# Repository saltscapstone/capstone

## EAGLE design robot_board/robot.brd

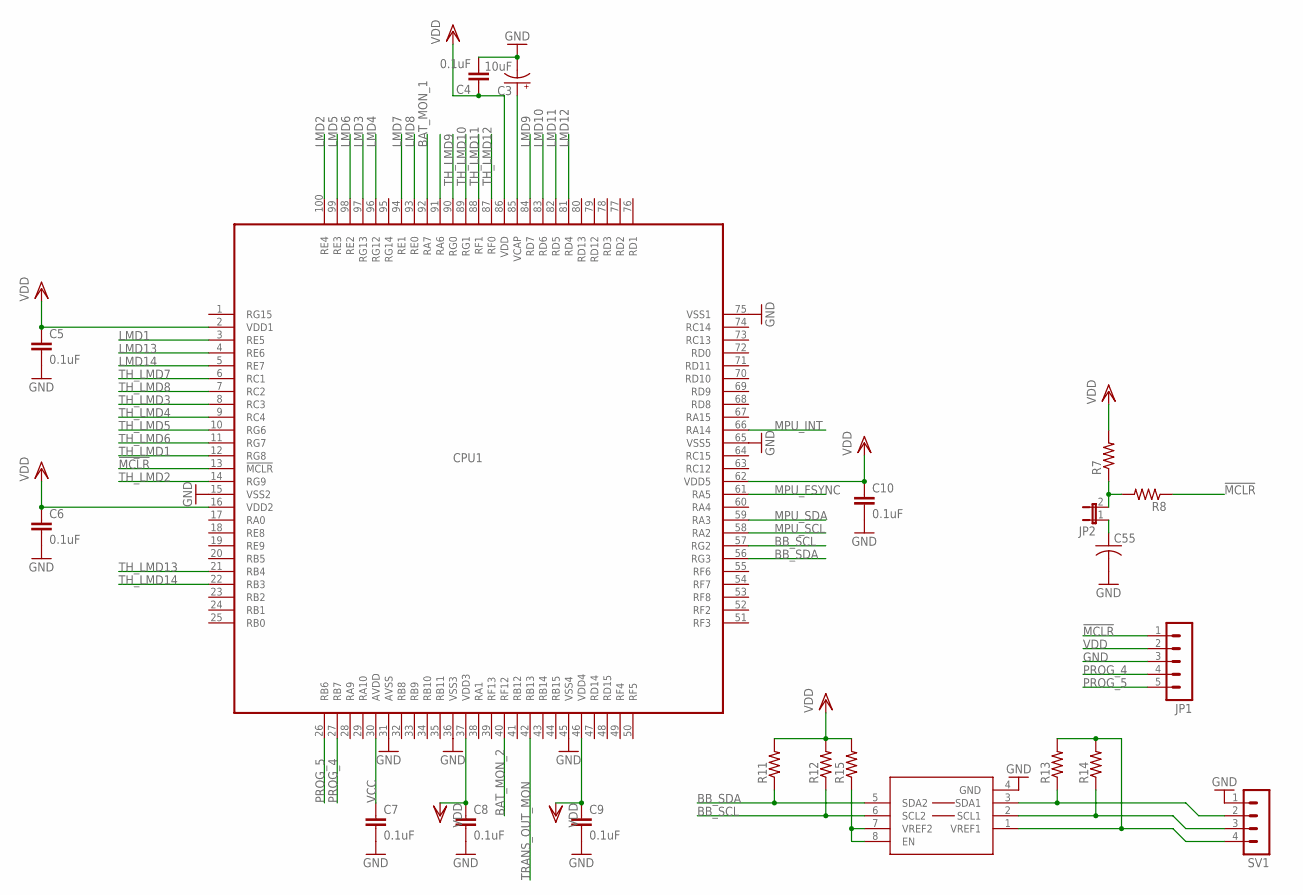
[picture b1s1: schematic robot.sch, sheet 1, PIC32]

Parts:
C3: 10uF; EIA3216
C4, C5, C6, C7, C8, C9, C10: 0.1uF; 0402-CAP
C55: C-USC0603; C0603
CPU1: DSPIC33FJ32GS610TQFP; TQFP100-14X14
JP1: MA05-1
JP2: JP1E; JP1
R7, R8, R11, R12, R13, R14, R15: R-US_R0603; R0603
SV1: MA04-1
U$17: PCA9306; PSOP-8

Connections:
!MCLR: CPU1.13 (!MCLR), JP1.1, R8.1
BAT_MON_1: CPU1.92 (RA7); also elsewhere on the board
BAT_MON_2: CPU1.40 (RF12); also elsewhere on the board
BB_SCL: CPU1.57 (RG2), R12.1, U$17.6 (SCL2)
BB_SDA: CPU1.56 (RG3), R11.1, U$17.5 (SDA2)
GND: C3.C (-), C4.2, C5.2, C6.2, C7.2, C8.2, C9.2, C10.2, C55.2, CPU1.15 (VSS2), CPU1.31 (AVSS), CPU1.36 (VSS3), CPU1.45 (VSS4), CPU1.65 (VSS5), CPU1.75 (VSS1), JP1.3, SV1.1, U$17.4 (GND); also elsewhere on the board
LMD1: CPU1.3 (RE5); also elsewhere on the board
LMD2: CPU1.100 (RE4); also elsewhere on the board
LMD3: CPU1.97 (RG13); also elsewhere on the board
LMD4: CPU1.96 (RG12); also elsewhere on the board
LMD5: CPU1.99 (RE3); also elsewhere on the board
LMD6: CPU1.98 (RE2); also elsewhere on the board
LMD7: CPU1.94 (RE1); also elsewhere on the board
LMD8: CPU1.93 (RE0); also elsewhere on the board
LMD9: CPU1.84 (RD7); also elsewhere on the board
LMD10: CPU1.83 (RD6); also elsewhere on the board
LMD11: CPU1.82 (RD5); also elsewhere on the board
LMD12: CPU1.81 (RD4); also elsewhere on the board
LMD13: CPU1.4 (RE6); also elsewhere on the board
LMD14: CPU1.5 (RE7); also elsewhere on the board
MPU_FSYNC: CPU1.61 (RA5); also elsewhere on the board
MPU_INT: CPU1.66 (RA14); also elsewhere on the board
MPU_SCL: CPU1.58 (RA2); also elsewhere on the board
MPU_SDA: CPU1.59 (RA3); also elsewhere on the board
unnamed: C3.A (+), CPU1.85 (VCAP)
unnamed: JP2.2, R7.1, R8.2
unnamed: C55.1, JP2.1
unnamed: R15.1, U$17.7 (VREF2), U$17.8 (EN)
unnamed: R13.1, SV1.2, U$17.3 (SDA1)
unnamed: R14.1, SV1.3, U$17.2 (SCL1)
unnamed: R13.2, R14.2, SV1.4, U$17.1 (VREF1)
PROG_4: CPU1.27 (RB7), JP1.4
PROG_5: CPU1.26 (RB6), JP1.5
TH_LMD1: CPU1.12 (RG8); also elsewhere on the board
TH_LMD2: CPU1.14 (RG9); also elsewhere on the board
TH_LMD3: CPU1.8 (RC3); also elsewhere on the board
TH_LMD4: CPU1.9 (RC4); also elsewhere on the board
TH_LMD5: CPU1.10 (RG6); also elsewhere on the board
TH_LMD6: CPU1.11 (RG7); also elsewhere on the board
TH_LMD7: CPU1.6 (RC1); also elsewhere on the board
TH_LMD8: CPU1.7 (RC2); also elsewhere on the board
TH_LMD9: CPU1.90 (RG0); also elsewhere on the board
TH_LMD10: CPU1.89 (RG1); also elsewhere on the board
TH_LMD11: CPU1.88 (RF1); also elsewhere on the board
TH_LMD12: CPU1.87 (RF0); also elsewhere on the board
TH_LMD13: CPU1.21 (RB4); also elsewhere on the board
TH_LMD14: CPU1.22 (RB3); also elsewhere on the board
TRANS_OUT_MON: CPU1.42 (RB13); also elsewhere on the board
VCC: C7.1, CPU1.30 (AVDD); also elsewhere on the board
VDD: C4.1, C5.1, C6.1, C8.1, C9.1, C10.1, CPU1.2 (VDD1), CPU1.16 (VDD2), CPU1.37 (VDD3), CPU1.46 (VDD4), CPU1.62 (VDD5), CPU1.86 (VDD), JP1.2, R7.2, R11.2, R12.2, R15.2; also elsewhere on the board

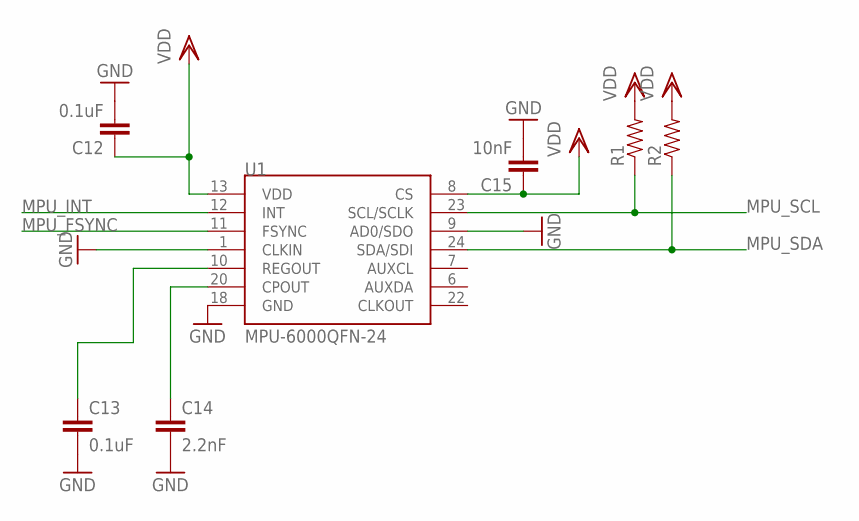
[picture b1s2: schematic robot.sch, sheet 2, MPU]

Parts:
C12, C13: 0.1uF; 0402-CAP
C14: 2.2nF; 0402-CAP
C15: 10nF; 0402-CAP
R1, R2: RESISTOR0603-RES; 0603-RES
U1: MPU-6000QFN-24; QFN-24-TESTING

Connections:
GND: C12.2, C13.2, C14.2, C15.2, U1.1 (CLKIN), U1.9 (AD0/SDO), U1.18 (GND); also elsewhere on the board
MPU_FSYNC: U1.11 (FSYNC); also elsewhere on the board
MPU_INT: U1.12 (INT); also elsewhere on the board
MPU_SCL: R1.1, U1.23 (SCL/SCLK); also elsewhere on the board
MPU_SDA: R2.1, U1.24 (SDA/SDI); also elsewhere on the board
unnamed: C14.1, U1.20 (CPOUT)
unnamed: C13.1, U1.10 (REGOUT)
VDD: C12.1, C15.1, R1.2, R2.2, U1.8 (CS), U1.13 (VDD); also elsewhere on the board

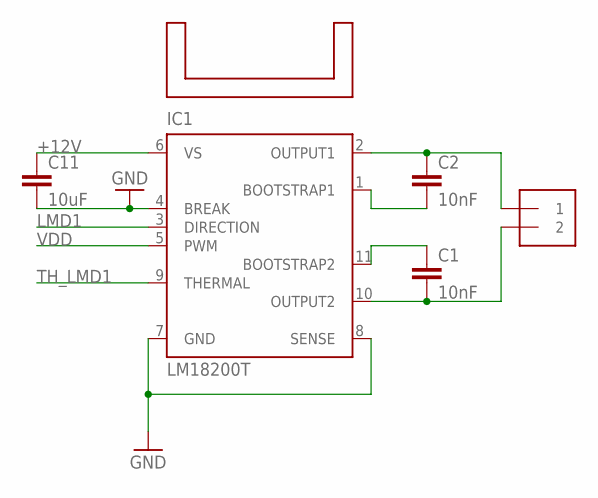
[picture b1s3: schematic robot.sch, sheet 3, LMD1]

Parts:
C1, C2: 10nF; 0402-CAP
C11: 10uF; 1206
IC1: LM18200T; TO-220-11
J13: 1X2-3.5MM
U$3: 593002B03400G

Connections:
+12V: C11.1, IC1.6 (VS); also elsewhere on the board
GND: C11.2, IC1.4 (BREAK), IC1.7 (GND), IC1.8 (SENSE); also elsewhere on the board
LMD1: IC1.3 (DIRECTION); also elsewhere on the board
unnamed: C2.1, IC1.2 (OUTPUT1), J13.1
unnamed: C2.2, IC1.1 (BOOTSTRAP1)
unnamed: C1.1, IC1.11 (BOOTSTRAP2)
unnamed: C1.2, IC1.10 (OUTPUT2), J13.2
TH_LMD1: IC1.9 (THERMAL); also elsewhere on the board
VDD: IC1.5 (PWM); also elsewhere on the board

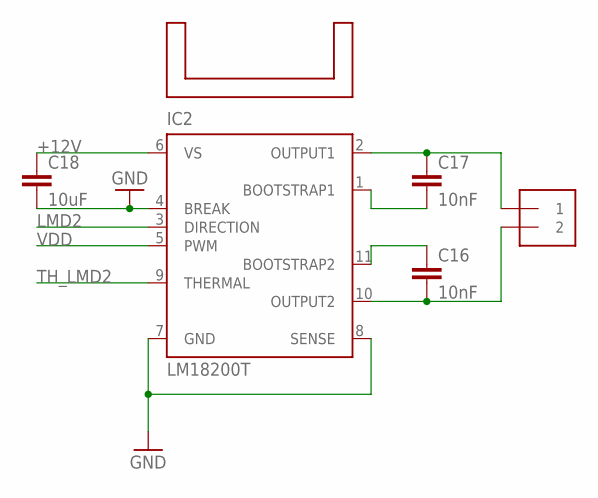
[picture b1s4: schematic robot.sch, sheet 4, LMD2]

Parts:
C16, C17: 10nF; 0402-CAP
C18: 10uF; 1206
IC2: LM18200T; TO-220-11
J2: 1X2-3.5MM
U$4: 593002B03400G

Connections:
+12V: C18.1, IC2.6 (VS); also elsewhere on the board
GND: C18.2, IC2.4 (BREAK), IC2.7 (GND), IC2.8 (SENSE); also elsewhere on the board
LMD2: IC2.3 (DIRECTION); also elsewhere on the board
unnamed: C17.1, IC2.2 (OUTPUT1), J2.1
unnamed: C17.2, IC2.1 (BOOTSTRAP1)
unnamed: C16.1, IC2.11 (BOOTSTRAP2)
unnamed: C16.2, IC2.10 (OUTPUT2), J2.2
TH_LMD2: IC2.9 (THERMAL); also elsewhere on the board
VDD: IC2.5 (PWM); also elsewhere on the board

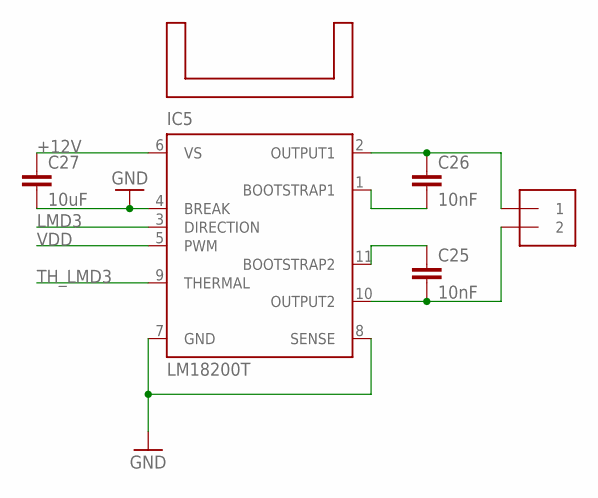
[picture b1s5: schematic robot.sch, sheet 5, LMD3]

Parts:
C25, C26: 10nF; 0402-CAP
C27: 10uF; 1206
IC5: LM18200T; TO-220-11
J5: 1X2-3.5MM
U$5: 593002B03400G

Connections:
+12V: C27.1, IC5.6 (VS); also elsewhere on the board
GND: C27.2, IC5.4 (BREAK), IC5.7 (GND), IC5.8 (SENSE); also elsewhere on the board
LMD3: IC5.3 (DIRECTION); also elsewhere on the board
unnamed: C26.1, IC5.2 (OUTPUT1), J5.1
unnamed: C26.2, IC5.1 (BOOTSTRAP1)
unnamed: C25.1, IC5.11 (BOOTSTRAP2)
unnamed: C25.2, IC5.10 (OUTPUT2), J5.2
TH_LMD3: IC5.9 (THERMAL); also elsewhere on the board
VDD: IC5.5 (PWM); also elsewhere on the board

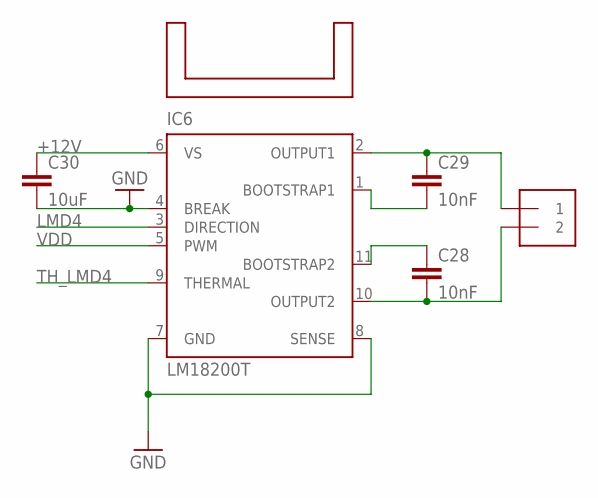
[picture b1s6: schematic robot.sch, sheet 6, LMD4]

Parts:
C28, C29: 10nF; 0402-CAP
C30: 10uF; 1206
IC6: LM18200T; TO-220-11
J6: 1X2-3.5MM
U$6: 593002B03400G

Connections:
+12V: C30.1, IC6.6 (VS); also elsewhere on the board
GND: C30.2, IC6.4 (BREAK), IC6.7 (GND), IC6.8 (SENSE); also elsewhere on the board
LMD4: IC6.3 (DIRECTION); also elsewhere on the board
unnamed: C29.1, IC6.2 (OUTPUT1), J6.1
unnamed: C29.2, IC6.1 (BOOTSTRAP1)
unnamed: C28.1, IC6.11 (BOOTSTRAP2)
unnamed: C28.2, IC6.10 (OUTPUT2), J6.2
TH_LMD4: IC6.9 (THERMAL); also elsewhere on the board
VDD: IC6.5 (PWM); also elsewhere on the board

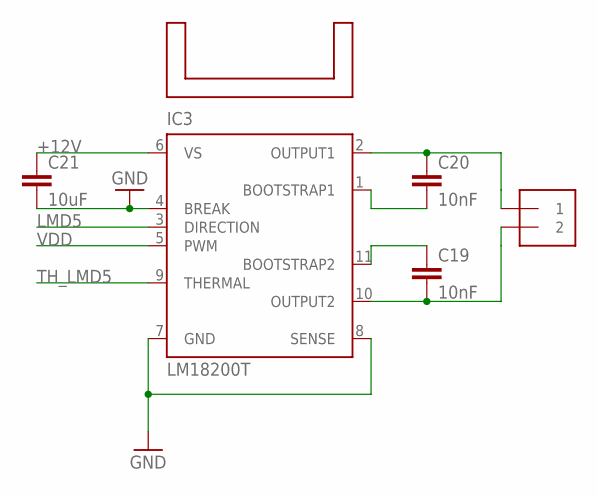
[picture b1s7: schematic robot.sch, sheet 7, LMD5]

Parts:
C19, C20: 10nF; 0402-CAP
C21: 10uF; 1206
IC3: LM18200T; TO-220-11
J3: 1X2-3.5MM
U$7: 593002B03400G

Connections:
+12V: C21.1, IC3.6 (VS); also elsewhere on the board
GND: C21.2, IC3.4 (BREAK), IC3.7 (GND), IC3.8 (SENSE); also elsewhere on the board
LMD5: IC3.3 (DIRECTION); also elsewhere on the board
unnamed: C20.1, IC3.2 (OUTPUT1), J3.1
unnamed: C20.2, IC3.1 (BOOTSTRAP1)
unnamed: C19.1, IC3.11 (BOOTSTRAP2)
unnamed: C19.2, IC3.10 (OUTPUT2), J3.2
TH_LMD5: IC3.9 (THERMAL); also elsewhere on the board
VDD: IC3.5 (PWM); also elsewhere on the board

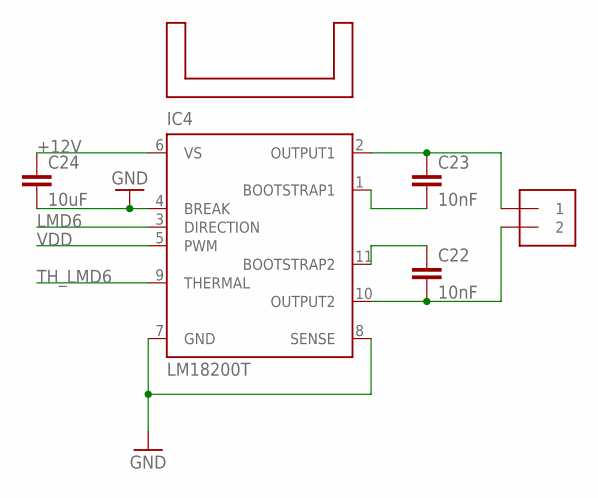
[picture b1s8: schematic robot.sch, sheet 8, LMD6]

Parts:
C22, C23: 10nF; 0402-CAP
C24: 10uF; 1206
IC4: LM18200T; TO-220-11
J4: 1X2-3.5MM
U$8: 593002B03400G

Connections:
+12V: C24.1, IC4.6 (VS); also elsewhere on the board
GND: C24.2, IC4.4 (BREAK), IC4.7 (GND), IC4.8 (SENSE); also elsewhere on the board
LMD6: IC4.3 (DIRECTION); also elsewhere on the board
unnamed: C23.1, IC4.2 (OUTPUT1), J4.1
unnamed: C23.2, IC4.1 (BOOTSTRAP1)
unnamed: C22.1, IC4.11 (BOOTSTRAP2)
unnamed: C22.2, IC4.10 (OUTPUT2), J4.2
TH_LMD6: IC4.9 (THERMAL); also elsewhere on the board
VDD: IC4.5 (PWM); also elsewhere on the board

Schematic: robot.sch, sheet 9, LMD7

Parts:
C31, C32: 10nF; 0402-CAP
C33: 10uF; 1206
IC7: LM18200T; TO-220-11
J7: 1X2-3.5MM
U$9: 593002B03400G

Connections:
+12V: C33.1, IC7.6 (VS); also elsewhere on the board
GND: C33.2, IC7.4 (BREAK), IC7.7 (GND), IC7.8 (SENSE); also elsewhere on the board
LMD7: IC7.3 (DIRECTION); also elsewhere on the board
unnamed: C32.1, IC7.2 (OUTPUT1), J7.1
unnamed: C32.2, IC7.1 (BOOTSTRAP1)
unnamed: C31.1, IC7.11 (BOOTSTRAP2)
unnamed: C31.2, IC7.10 (OUTPUT2), J7.2
TH_LMD7: IC7.9 (THERMAL); also elsewhere on the board
VDD: IC7.5 (PWM); also elsewhere on the board

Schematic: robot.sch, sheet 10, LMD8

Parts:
C34, C35: 10nF; 0402-CAP
C36: 10uF; 1206
IC8: LM18200T; TO-220-11
J8: 1X2-3.5MM
U$10: 593002B03400G

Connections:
+12V: C36.1, IC8.6 (VS); also elsewhere on the board
GND: C36.2, IC8.4 (BREAK), IC8.7 (GND), IC8.8 (SENSE); also elsewhere on the board
LMD8: IC8.3 (DIRECTION); also elsewhere on the board
unnamed: C35.1, IC8.2 (OUTPUT1), J8.1
unnamed: C35.2, IC8.1 (BOOTSTRAP1)
unnamed: C34.1, IC8.11 (BOOTSTRAP2)
unnamed: C34.2, IC8.10 (OUTPUT2), J8.2
TH_LMD8: IC8.9 (THERMAL); also elsewhere on the board
VDD: IC8.5 (PWM); also elsewhere on the board

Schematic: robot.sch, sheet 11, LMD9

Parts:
C37, C38: 10nF; 0402-CAP
C39: 10uF; 1206
IC9: LM18200T; TO-220-11
J9: 1X2-3.5MM
U$11: 593002B03400G

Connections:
+12V: C39.1, IC9.6 (VS); also elsewhere on the board
GND: C39.2, IC9.4 (BREAK), IC9.7 (GND), IC9.8 (SENSE); also elsewhere on the board
LMD9: IC9.3 (DIRECTION); also elsewhere on the board
unnamed: C38.1, IC9.2 (OUTPUT1), J9.1
unnamed: C38.2, IC9.1 (BOOTSTRAP1)
unnamed: C37.1, IC9.11 (BOOTSTRAP2)
unnamed: C37.2, IC9.10 (OUTPUT2), J9.2
TH_LMD9: IC9.9 (THERMAL); also elsewhere on the board
VDD: IC9.5 (PWM); also elsewhere on the board

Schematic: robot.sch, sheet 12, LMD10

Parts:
C40, C41: 10nF; 0402-CAP
C42: 10uF; 1206
IC10: LM18200T; TO-220-11
J10: 1X2-3.5MM
U$12: 593002B03400G

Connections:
+12V: C42.1, IC10.6 (VS); also elsewhere on the board
GND: C42.2, IC10.4 (BREAK), IC10.7 (GND), IC10.8 (SENSE); also elsewhere on the board
LMD10: IC10.3 (DIRECTION); also elsewhere on the board
unnamed: C41.1, IC10.2 (OUTPUT1), J10.1
unnamed: C41.2, IC10.1 (BOOTSTRAP1)
unnamed: C40.1, IC10.11 (BOOTSTRAP2)
unnamed: C40.2, IC10.10 (OUTPUT2), J10.2
TH_LMD10: IC10.9 (THERMAL); also elsewhere on the board
VDD: IC10.5 (PWM); also elsewhere on the board

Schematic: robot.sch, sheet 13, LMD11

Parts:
C43, C44: 10nF; 0402-CAP
C45: 10uF; 1206
IC11: LM18200T; TO-220-11
J11: 1X2-3.5MM
U$13: 593002B03400G

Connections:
+12V: C45.1, IC11.6 (VS); also elsewhere on the board
GND: C45.2, IC11.4 (BREAK), IC11.7 (GND), IC11.8 (SENSE); also elsewhere on the board
LMD11: IC11.3 (DIRECTION); also elsewhere on the board
unnamed: C44.1, IC11.2 (OUTPUT1), J11.1
unnamed: C44.2, IC11.1 (BOOTSTRAP1)
unnamed: C43.1, IC11.11 (BOOTSTRAP2)
unnamed: C43.2, IC11.10 (OUTPUT2), J11.2
TH_LMD11: IC11.9 (THERMAL); also elsewhere on the board
VDD: IC11.5 (PWM); also elsewhere on the board

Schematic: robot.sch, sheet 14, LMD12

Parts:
C46, C47: 10nF; 0402-CAP
C48: 10uF; 1206
IC12: LM18200T; TO-220-11
J14: 1X2-3.5MM
U$14: 593002B03400G

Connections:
+12V: C48.1, IC12.6 (VS); also elsewhere on the board
GND: C48.2, IC12.4 (BREAK), IC12.7 (GND), IC12.8 (SENSE); also elsewhere on the board
LMD12: IC12.3 (DIRECTION); also elsewhere on the board
unnamed: C47.1, IC12.2 (OUTPUT1), J14.1
unnamed: C47.2, IC12.1 (BOOTSTRAP1)
unnamed: C46.1, IC12.11 (BOOTSTRAP2)
unnamed: C46.2, IC12.10 (OUTPUT2), J14.2
TH_LMD12: IC12.9 (THERMAL); also elsewhere on the board
VDD: IC12.5 (PWM); also elsewhere on the board

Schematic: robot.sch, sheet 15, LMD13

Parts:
C49, C50: 10nF; 0402-CAP
C51: 10uF; 1206
IC13: LM18200T; TO-220-11
J15: 1X2-3.5MM
U$15: 593002B03400G

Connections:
+12V: C51.1, IC13.6 (VS); also elsewhere on the board
GND: C51.2, IC13.4 (BREAK), IC13.7 (GND), IC13.8 (SENSE); also elsewhere on the board
LMD13: IC13.3 (DIRECTION); also elsewhere on the board
unnamed: C50.1, IC13.2 (OUTPUT1), J15.1
unnamed: C50.2, IC13.1 (BOOTSTRAP1)
unnamed: C49.1, IC13.11 (BOOTSTRAP2)
unnamed: C49.2, IC13.10 (OUTPUT2), J15.2
TH_LMD13: IC13.9 (THERMAL); also elsewhere on the board
VDD: IC13.5 (PWM); also elsewhere on the board

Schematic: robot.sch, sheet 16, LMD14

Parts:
C52, C53: 10nF; 0402-CAP
C54: 10uF; 1206
IC14: LM18200T; TO-220-11
J16: 1X2-3.5MM
U$16: 593002B03400G

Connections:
+12V: C54.1, IC14.6 (VS); also elsewhere on the board
GND: C54.2, IC14.4 (BREAK), IC14.7 (GND), IC14.8 (SENSE); also elsewhere on the board
LMD14: IC14.3 (DIRECTION); also elsewhere on the board
unnamed: C53.1, IC14.2 (OUTPUT1), J16.1
unnamed: C53.2, IC14.1 (BOOTSTRAP1)
unnamed: C52.1, IC14.11 (BOOTSTRAP2)
unnamed: C52.2, IC14.10 (OUTPUT2), J16.2
TH_LMD14: IC14.9 (THERMAL); also elsewhere on the board
VDD: IC14.5 (PWM); also elsewhere on the board

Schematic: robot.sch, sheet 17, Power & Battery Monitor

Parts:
I1: FB
J1, J12, J17, J18, J19, J20: 1X2-3.5MM
R3, R4, R5, R6, R9, R10: R-US_R0603; R0603

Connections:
+12V: J12.2, J17.2, J20.2, R3.1; also elsewhere on the board
+12V1: J18.2, R5.2
BAT_MON_1: R3.2, R4.2; also elsewhere on the board
BAT_MON_2: R5.1, R6.1; also elsewhere on the board
GND: J1.1, J12.1, J17.1, J18.1, J19.1, J20.1, R4.1, R6.2, R10.1; also elsewhere on the board
TRANSFORMER_IN: J19.2, R9.1
TRANS_OUT_MON: R9.2, R10.2; also elsewhere on the board
VCC: I1.P$2 (2); also elsewhere on the board
VDD: I1.P$1 (1), J1.2; also elsewhere on the board

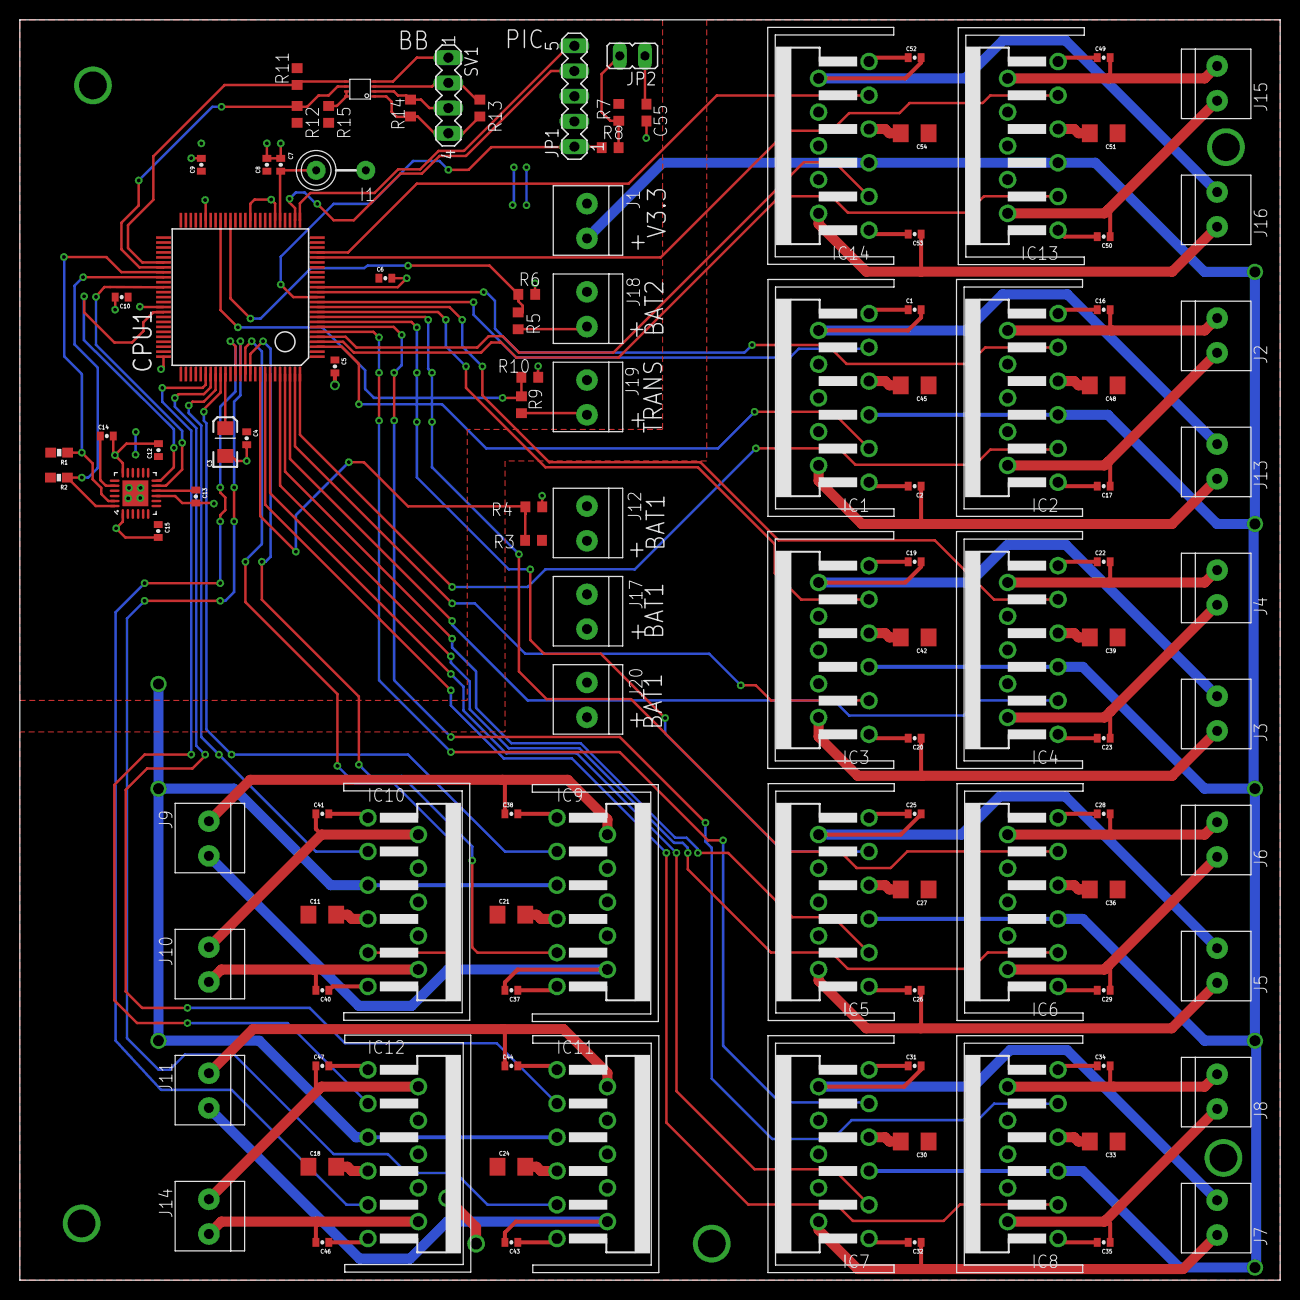
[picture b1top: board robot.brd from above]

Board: 2 copper layers, 127.0 x 127.0 mm, 125 parts (0 on the bottom side), 111 nets.

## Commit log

2013-04-26 More stuff

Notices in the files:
parts and their libraries:
SparkFun-Sensors: Licensing: CC v3.0 Share-Alike You are welcome to use this library for commercial purposes.
